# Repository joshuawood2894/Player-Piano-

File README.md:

# Player-Piano-
Senior Design Project 2018-2019

Fall 2018/Spring 2019 senior project for the University of Texas in Tyler. Project features a hardware interface that allows a user to control an array of 96 linear solenoids using both MIDI (via micro SD card) and four channels of CV/Gate functionality. Project uses a Teensy 3.6 developement board with its Arm Cortex M4 to control entire real-time system. Repository includes source code and KiCad files (schematic view, PCB view, and Gerber files).

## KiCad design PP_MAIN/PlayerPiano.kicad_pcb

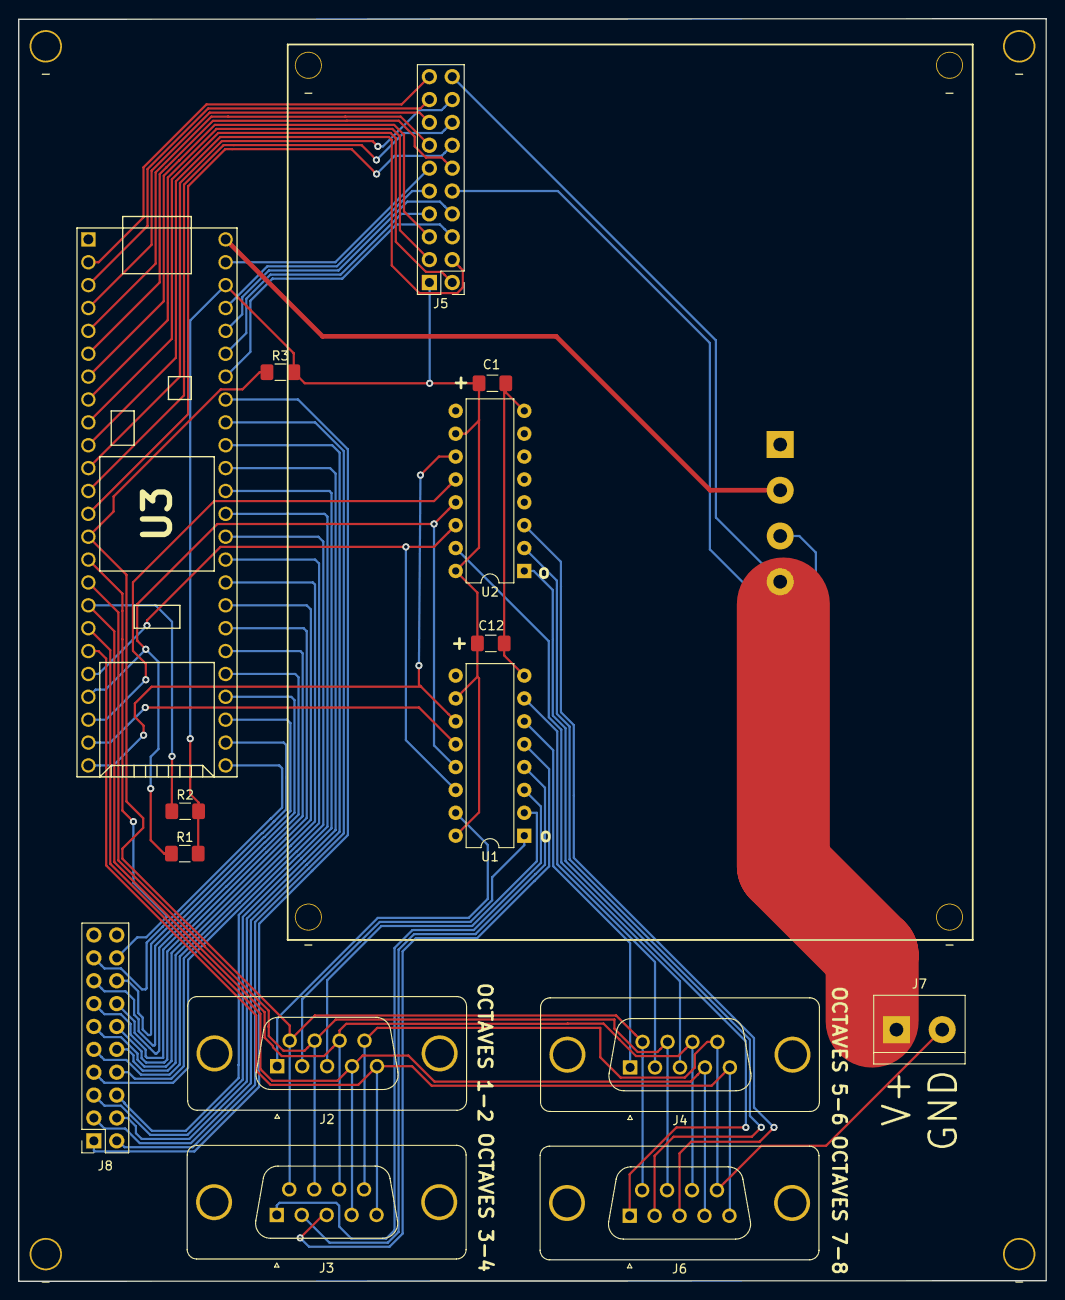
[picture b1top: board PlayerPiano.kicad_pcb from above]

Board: 2 copper layers, 114.1 x 140.2 mm, 24 parts (1 on the bottom side), 61 nets.

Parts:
C1: CP1; C_1206_3216Metric_Pad1.42x1.75mm_HandSolder
C12: 100n; C_1206_3216Metric_Pad1.42x1.75mm_HandSolder
J1: Screw_Terminal_01x04; TerminalBlock_bornier-4_P5.08mm
J2, J3, J4, J6: Conn_01x09; DSUB-9_Female_Vertical_P2.77x2.84mm_MountingHoles
J5: Conn_02x10_Counter_Clockwise; PinHeader_2x10_P2.54mm_Vertical
J7: Screw_Terminal_01x02; TerminalBlock_bornier-2_P5.08mm
J8: Conn_02x10_Counter_Clockwise; PinSocket_2x10_P2.54mm_Vertical
R1, R2, R3: 47k; R_1206_3216Metric_Pad1.42x1.75mm_HandSolder
U1, U2: 74HC595; DIP-16_W7.62mm
U3: Teensy3.6; Teensy35_36
_: PP_Screw
_#2, _#3, _#4, _#5, _#6, _#7, _#8: PP_Screw

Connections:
/+3V3: C1.1, C12.1, J5.1, R1.2, R2.2, R3.2, U1.10, U1.16, U2.10, U2.16, U3.51
/+5V: J1.2, U3.53
/+12V: J1.4, J5.20, J7.1
/-12V: J1.3, J5.10
/GND: C1.2, C12.2, J1.1, J2.9, J3.9, J4.9, J5.11, J6.9, J7.2, U1.8, U2.8, U3.1, U3.52
Enc_A: J5.19, U3.2
Enc_B: J5.18, U3.11
Enc_SW: J5.17, U3.3
FAULT: J2.6, J3.6, J4.6, J6.6, R3.1, U3.14
Gate_A: J5.2, U3.9
Gate_B: J5.3, U3.8
Gate_C: J5.4, U3.10
Gate_D: J5.5, U3.7
Midi_Play_Pause: J5.16, U3.12
Midi_Stop: J5.15, U3.4
Midi_loop: J5.14, U3.13
unnamed: J2.1, U1.15
unnamed: J2.2, U1.1
unnamed: J2.3, U1.2
unnamed: J3.1, U1.3
unnamed: J3.2, U1.4
unnamed: J3.3, U1.5
unnamed: J4.1, U1.6
unnamed: J4.2, U1.7
unnamed: J4.3, U2.15
unnamed: J6.1, U2.1
unnamed: J6.2, U2.2
unnamed: J6.3, U2.3
unnamed: J8.1, U3.46
unnamed: J8.2, U3.45
unnamed: J8.3, U3.44
unnamed: J8.4, U3.43
unnamed: J8.5, U3.42
unnamed: J8.6, U3.41
unnamed: J8.7, U3.40
unnamed: J8.8, U3.39
unnamed: J8.9, U3.38
unnamed: J8.10, U3.37
unnamed: J8.11, U3.36
unnamed: J8.12, U3.35
unnamed: J8.13, U3.34
unnamed: J8.14, U3.33
unnamed: J8.15, U3.32
unnamed: J8.16, U3.31
unnamed: J8.17, U3.30
PITCH_A: J5.6, U3.47
PITCH_B: J5.7, U3.48
PITCH_C: J5.8, U3.49
PITCH_D: J5.9, U3.50
RESET: J2.7, J3.7, J4.7, J6.7, U3.16
SCL_Display: J5.13, U3.5
SDA_Display: J5.12, U3.6
SER_CLK: J2.4, J3.4, J4.4, J6.4, U3.18
SER_DATA: J2.5, J3.5, J4.5, J6.5, U3.19
SRSEL_CLK: U1.11, U2.11, U3.24
SRSEL_DATA: U1.14, U2.14, U3.20
SRSEL_ENABLE: R1.1, U1.13, U2.13, U3.21
SRSEL_LATCH_A: U1.12, U3.23
SRSEL_LATCH_B: U2.12, U3.22
nENBL: J2.8, J3.8, J4.8, J6.8, R2.1, U3.17
xtra_3V3: J8.18, U3.15

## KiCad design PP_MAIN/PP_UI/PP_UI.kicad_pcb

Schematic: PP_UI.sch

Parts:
C1, C2, C3, C4: 1n; C_1206_3216Metric_Pad1.42x1.75mm_HandSolder
C5, C6, C7, C8, C9, C10: .01u; C_1206_3216Metric_Pad1.42x1.75mm_HandSolder
C11, C12, C13: 100n; CP_EIA-3216-18_Kemet-A_Pad1.58x1.35mm_HandSolder
J1, J2, J3, J4, J6, J7, J8, J9: AudioJack2_Ground_Switch; THONKICONN
J5: Conn_01x04_Female; PinHeader_1x04_P2.54mm_Vertical
J10: Conn_02x10_Counter_Clockwise; PinHeader_2x10_P2.54mm_Vertical
J11, J12, J13, J14, J15, J16, J17, J18, J19, J20, J21, J22, J23, J24: Conn_02x12_Odd_Even; PinHeader_2x12_P2.54mm_Vertical
Q1, Q2, Q3, Q4: 2N7000; TO-92_Inline
R1, R2, R3, R4: 100k; R_1206_3216Metric_Pad1.42x1.75mm_HandSolder
R5, R6, R7, R8, R9, R10, R11, R12, R13, R14, R15, R16: 24.9k; R_1206_3216Metric_Pad1.42x1.75mm_HandSolder
R17, R18, R19, R20, R21, R22, R23, R24, R25, R26, R29, R30: 10k; R_1206_3216Metric_Pad1.42x1.75mm_HandSolder
R27, R28, R31, R32: 47k; R_1206_3216Metric_Pad1.42x1.75mm_HandSolder
SW1, SW2, SW3: SW_Push; Push_E-Switch_KS01Q01
SW4: Rotary_Encoder_Switch; RotaryEncoder_Alps_EC11E-Switch_Vertical_H20mm
U1: TL074; DIP-14_W8.89mm_SMDSocket_LongPads
U2: MCP6004; DIP-14_W8.89mm_SMDSocket_LongPads
U3: 40106; DIP-14_W8.89mm_SMDSocket_LongPads

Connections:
/+3V3: C11.1, C13.1, J5.1, J10.1, Q1.3, Q2.3, Q3.3, Q4.3, R17.2, R18.2, R19.2, R23.2, R24.2, R29.1, U2.4 (V+), U3.14
/GND: C5.2, C6.2, C7.2, C8.2, C9.2, C10.2, C11.2, C13.2, J5.2, J10.11, R27.2, R28.2, R31.2, R32.2, SW1.1, SW2.1, SW3.1, SW4.C, SW4.S2, U1.2 (-), U1.6 (-), U1.9 (-), U1.13 (-), U2.2 (-), U2.6 (-), U2.9 (-), U2.11 (V-), U2.13 (-), U3.7
/VCC: C12.1, J10.20, U1.4 (V+)
/VEE: C12.2, J10.10, U1.11 (V-)
Enc_A: J10.19, U3.4
Enc_B: J10.18, U3.6
Enc_SW: J10.17, U3.2
Gate_A: J10.2, Q1.1, R27.1
Gate_B: J10.3, Q3.1, R31.1
Gate_C: J10.4, Q2.1, R28.1
Gate_D: J10.5, Q4.1, R32.1
Midi_Play_Pause: J10.16, U3.12
Midi_Stop: J10.15, U3.8
Midi_loop: J10.14, U3.10
unnamed: C1.2, R9.1, R13.2, U2.3 (+)
unnamed: C2.2, R10.1, R14.2, U2.5 (+)
unnamed: C3.2, R11.1, R15.2, U2.10 (+)
unnamed: C4.2, R12.1, R16.2, U2.12 (+)
unnamed: C5.1, R20.1, U3.13
unnamed: C6.1, R21.1, U3.9
unnamed: C7.1, R22.1, U3.11
unnamed: C8.1, R25.2, U3.3
unnamed: C9.1, R26.2, U3.5
unnamed: C10.1, R30.1, U3.1
unnamed: J11.1, J17.1
unnamed: J11.2, J17.2
unnamed: J11.3, J17.3
unnamed: J11.4, J17.4
unnamed: J11.5, J17.5
unnamed: J11.6, J17.6
unnamed: J11.7, J17.7
unnamed: J11.8, J17.8
unnamed: J11.9, J17.9
unnamed: J11.10, J17.10
unnamed: J11.11, J17.11
unnamed: J11.12, J17.12
unnamed: J11.13, J17.13
unnamed: J11.14, J17.14
unnamed: J11.15, J17.15
unnamed: J11.16, J17.16
unnamed: J11.17, J17.17
unnamed: J11.18, J17.18
unnamed: J11.19, J17.19
unnamed: J11.20, J17.20
unnamed: J11.21, J17.21
unnamed: J11.22, J17.22
unnamed: J11.23, J17.23
unnamed: J11.24, J17.24
unnamed: R1.1, R5.2, U1.3 (+)
unnamed: R2.1, R6.2, U1.5 (+)
unnamed: R3.1, R7.2, U1.10 (+)
unnamed: R4.1, R8.2, U1.12 (+)
unnamed: R5.1, R9.2, U1.1
unnamed: R6.1, R10.2, U1.7
unnamed: R7.1, R11.2, U1.8
unnamed: R8.1, R12.2, U1.14
unnamed: R17.1, R20.2, SW1.2
unnamed: R18.1, R21.2, SW2.2
unnamed: R19.1, R22.2, SW3.2
unnamed: R23.1, R25.1, SW4.A
unnamed: R24.1, R26.1, SW4.B
unnamed: R29.2, R30.2, SW4.S1
PITCH_A: C1.1, J10.6, R13.1, U2.1
PITCH_B: C2.1, J10.7, R14.1, U2.7
PITCH_C: C3.1, J10.8, R15.1, U2.8
PITCH_D: C4.1, J10.9, R16.1, U2.14
SCL_Display: J5.3, J10.13
SDA_Display: J5.4, J10.12

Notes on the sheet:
MIDI BUTTONS
ENCODER W/ SW
GATE INPUTS
CV INPUTS
DISPLAY
OCTAVE TEMINALS

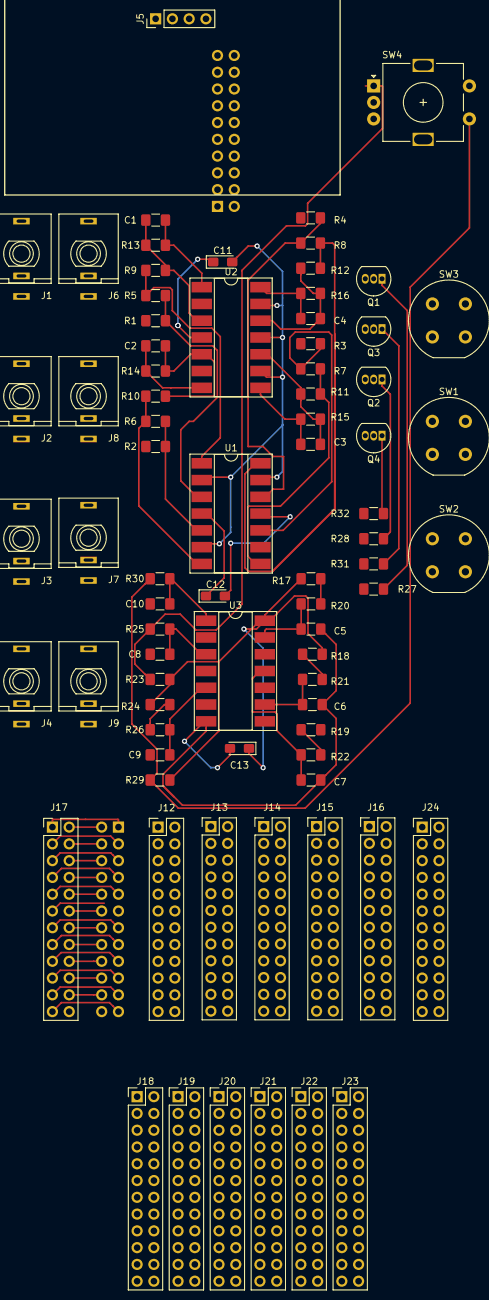
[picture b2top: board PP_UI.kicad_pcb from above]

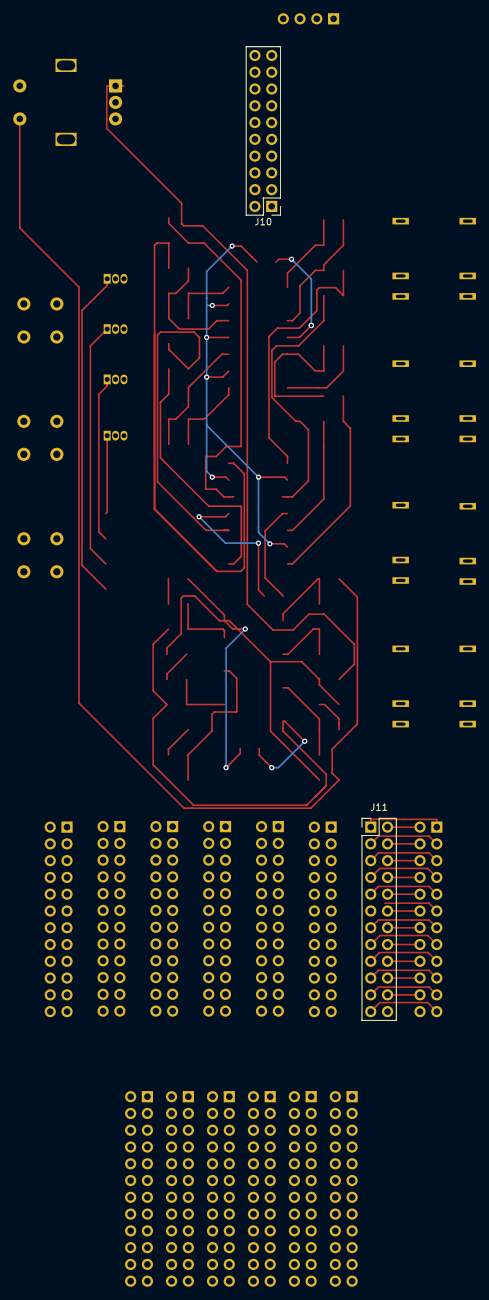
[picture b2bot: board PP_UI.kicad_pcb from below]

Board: 2 copper layers, 80 parts (2 on the bottom side), 68 nets.

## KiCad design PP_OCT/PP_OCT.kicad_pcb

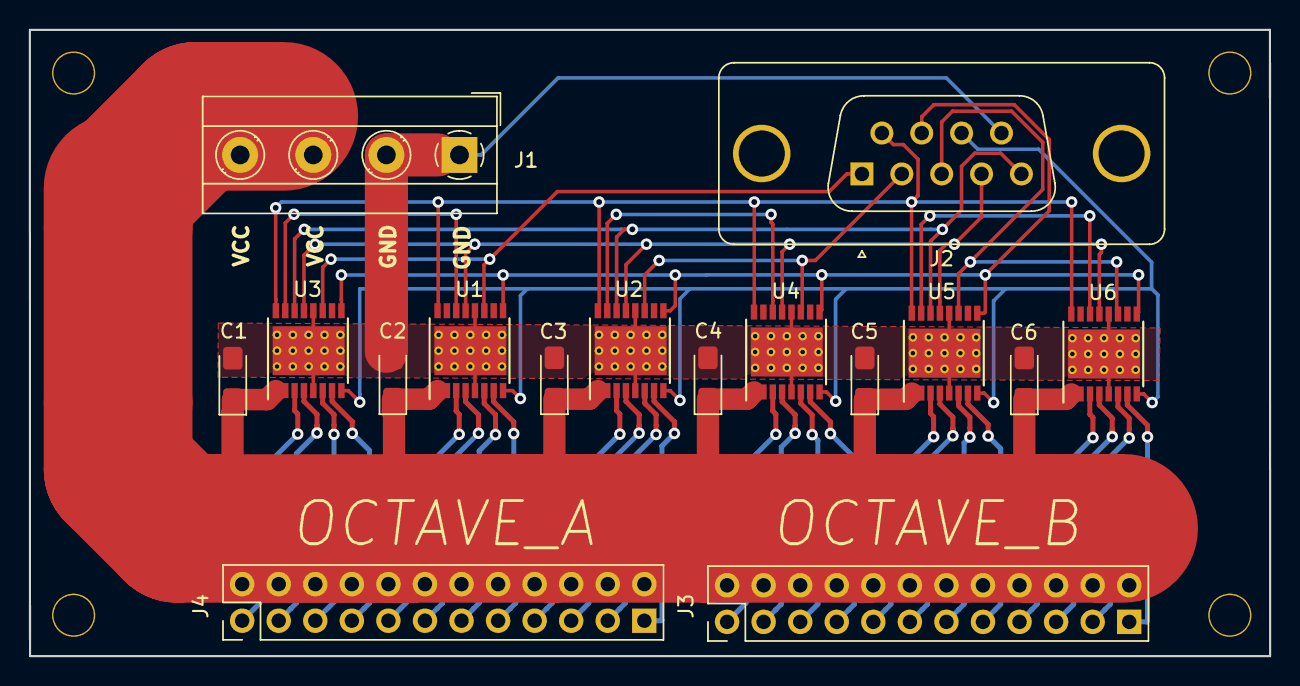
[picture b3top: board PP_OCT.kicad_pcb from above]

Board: 2 copper layers, 86.2 x 43.5 mm, 16 parts (0 on the bottom side), 37 nets.

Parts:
C1, C2, C3, C4, C5, C6: CP; CP_EIA-3216-10_Kemet-I_Pad1.58x1.35mm_HandSolder
J1: Screw_Terminal_01x04; TerminalBlock_MetzConnect_Type101_RT01604HBWC_1x04_P5.08mm_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
J2: Conn_01x09; DSUB-9_Female_Vertical_P2.77x2.84mm_MountingHoles
J3, J4: Conn_02x12_Odd_Even; PinSocket_2x12_P2.54mm_Vertical
U1, U2, U3, U4, U5, U6: DRV8804; HTSSOP-16-1EP_4.4x5mm_P0.65mm_EP3.4x5mm_Mask3x3mm_ThermalVi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

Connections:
/GND: C1.2, C2.2, C3.2, C4.2, C5.2, C6.2, J1.1, J1.2, J2.9, U1.5, U1.12, U1.17, U2.5, U2.12, U2.17, U3.5, U3.12, U3.17, U4.5, U4.12, U4.17, U5.5, U5.12, U5.17, U6.5, U6.12, U6.17
/VCC: C1.1, C2.1, C3.1, C4.1, C5.1, C6.1, J1.3, J1.4, J3.2, J3.4, J3.6, J3.8, J3.10, J3.12, J3.14, J3.16, J3.18, J3.20, J3.22, J3.24, J4.2, J4.4, J4.6, J4.8, J4.10, J4.12, J4.14, J4.16, J4.18, J4.20, J4.22, J4.24, U1.1, U1.2, U2.1, U2.2, U3.1, U3.2, U4.1, U4.2, U5.1, U5.2, U6.1, U6.2
FAULT: J2.6, U1.16, U2.16, U3.16, U4.16, U5.16, U6.16
LATCH_A: J2.1, U1.11, U3.11
LATCH_B: J2.2, U2.11, U4.11
LATCH_C: J2.3, U5.11, U6.11
unnamed: J3.1, U6.7
unnamed: J3.3, U6.6
unnamed: J3.5, U6.4
unnamed: J3.7, U6.3
unnamed: J3.9, U5.7
unnamed: J3.11, U5.6
unnamed: J3.13, U5.4
unnamed: J3.15, U5.3
unnamed: J3.17, U4.7
unnamed: J3.19, U4.6
unnamed: J3.21, U4.4
unnamed: J3.23, U4.3
unnamed: J4.1, U2.7
unnamed: J4.3, U2.6
unnamed: J4.5, U2.4
unnamed: J4.7, U2.3
unnamed: J4.9, U1.7
unnamed: J4.11, U1.6
unnamed: J4.13, U1.4
unnamed: J4.15, U1.3
unnamed: J4.17, U3.7
unnamed: J4.19, U3.6
unnamed: J4.21, U3.4
unnamed: J4.23, U3.3
unnamed: U1.14, U3.15
unnamed: U2.15, U4.14
unnamed: U5.15, U6.14
RESET: J2.7, U1.9, U2.9, U3.9, U4.9, U5.9, U6.9
SER_CLK: J2.4, U1.13, U2.13, U3.13, U4.13, U5.13, U6.13
SER_DATA: J2.5, U2.14, U3.14, U5.14
nENBL: J2.8, U1.8, U2.8, U3.8, U4.8, U5.8, U6.8

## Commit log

2019-04-29 Arduino Sketch File
2019-04-29 KiCad files for OCTAVE PCB
2019-04-29 KiCad files for USER INTERFACE PCB
2019-04-29 KiCad files for MAIN PCB
2019-04-29 Gerber and Drill files for all three PCBs
2019-04-29 Documentation (bill of materials, user manual, etc.)
